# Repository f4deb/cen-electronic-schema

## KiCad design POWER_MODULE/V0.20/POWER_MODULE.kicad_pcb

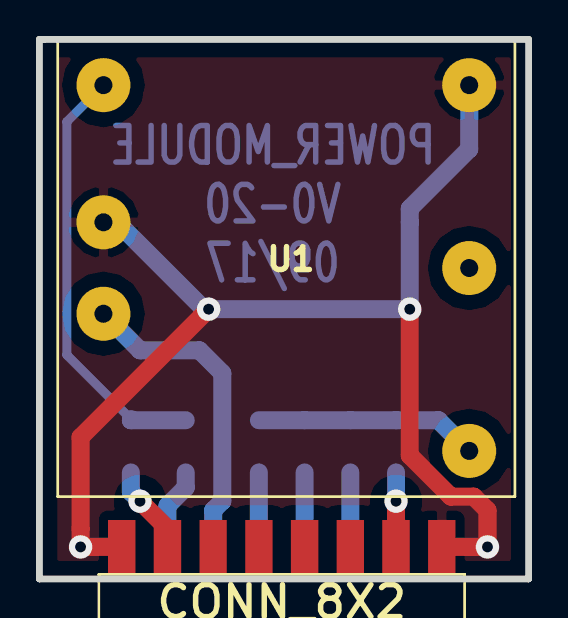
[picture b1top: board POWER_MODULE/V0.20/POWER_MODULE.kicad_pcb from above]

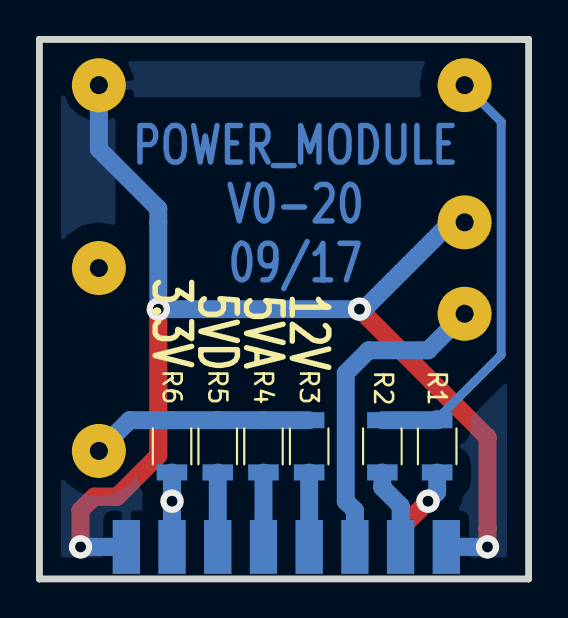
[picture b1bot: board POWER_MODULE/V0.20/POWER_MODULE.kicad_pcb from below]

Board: 2 copper layers, 27.2 x 30.0 mm, 8 parts (6 on the bottom side), 10 nets.

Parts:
P1: CONN_8X2; HE10-16-F-2
R1, R2, R3, R4, R5, R6: 0; R_1206
U1: TRACO-THN-15-1211

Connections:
+3V3: P1.13, P1.14, R6.1
+5V: P1.11, P1.12, R5.1
+5VA: P1.9, P1.10, R4.1
+12V: P1.7, P1.8, R3.1
+BATT: P1.5, P1.6, U1.1
/RA: P1.3, R1.1
/RD: P1.4, R2.1
GND: P1.1, P1.2, P1.15, P1.16, U1.2, U1.5
unnamed: R1.2, R2.2, U1.6
unnamed: R3.2, R4.2, R5.2, R6.2, U1.3

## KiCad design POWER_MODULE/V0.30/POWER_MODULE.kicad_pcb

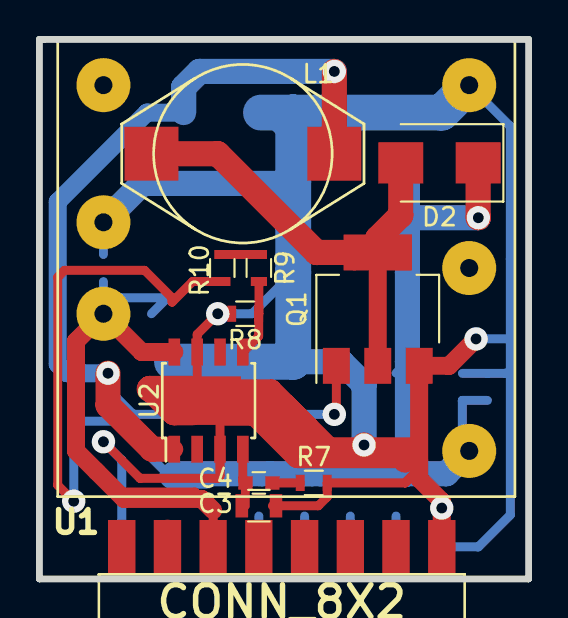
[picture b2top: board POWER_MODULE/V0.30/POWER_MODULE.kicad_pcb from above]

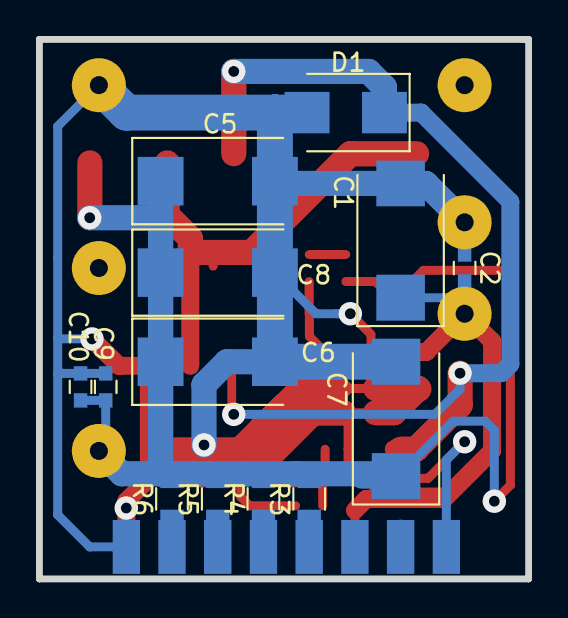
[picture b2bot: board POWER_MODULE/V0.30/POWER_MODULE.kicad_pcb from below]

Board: 2 copper layers, 27.2 x 30.0 mm, 25 parts (13 on the bottom side), 13 nets.

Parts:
C1, C6, C7, C8: 22µ/35V; CP_Tantalum_Case-D_EIA-7343-31_Reflow
C2: 47n; C_0603
C3: 220p; R_0805
C4: 22n; C_0603
C5: 100µ/16V; CP_Tantalum_Case-D_EIA-7343-31_Reflow
C9, C10: 100n; C_0603
D1, D2: MBRS130LT3G; D_SMB
L1: INDUCTOR; self_cms_we-pd3
P1: CONN_8X2; HE10-16-F-2
Q1: IRLL3303; SOT-223
R3, R4, R5, R6: 0; R_0805
R7: 4.7k; R_0603
R8, R9, R10: R; R_0603
U1: TRACO-THN-15-1211
U2: L5973D; Diodes_PSOP-8

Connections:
+3V3: P1.13, P1.14, R6.1
+5V: P1.11, P1.12, R5.1
+5VA: P1.9, P1.10, R4.1
+12V: P1.7, P1.8, R3.1
+BATT: C1.1, C2.1, P1.5, P1.6, U1.1, U2.8
GND: C1.2, C2.2, C3.2, C5.2, C6.2, C7.2, C8.2, C9.2, C10.2, D1.2, P1.1, P1.2, P1.15, P1.16, Q1.3, R7.2, R8.2, U1.2, U1.5, U2.3, U2.7, U2.9
unnamed: C3.1, C4.1, U2.4
unnamed: C4.2, R7.1
unnamed: C5.1, C6.1, C7.1, C8.1, C9.1, C10.1, D2.1, R3.2, R4.2, R5.2, R6.2, R10.1, U1.3
unnamed: D1.1, L1.1, Q1.1, U2.1
unnamed: D2.2, L1.2, Q1.2, Q1.4
unnamed: R8.1, R9.2, U2.5
unnamed: R9.1, R10.2

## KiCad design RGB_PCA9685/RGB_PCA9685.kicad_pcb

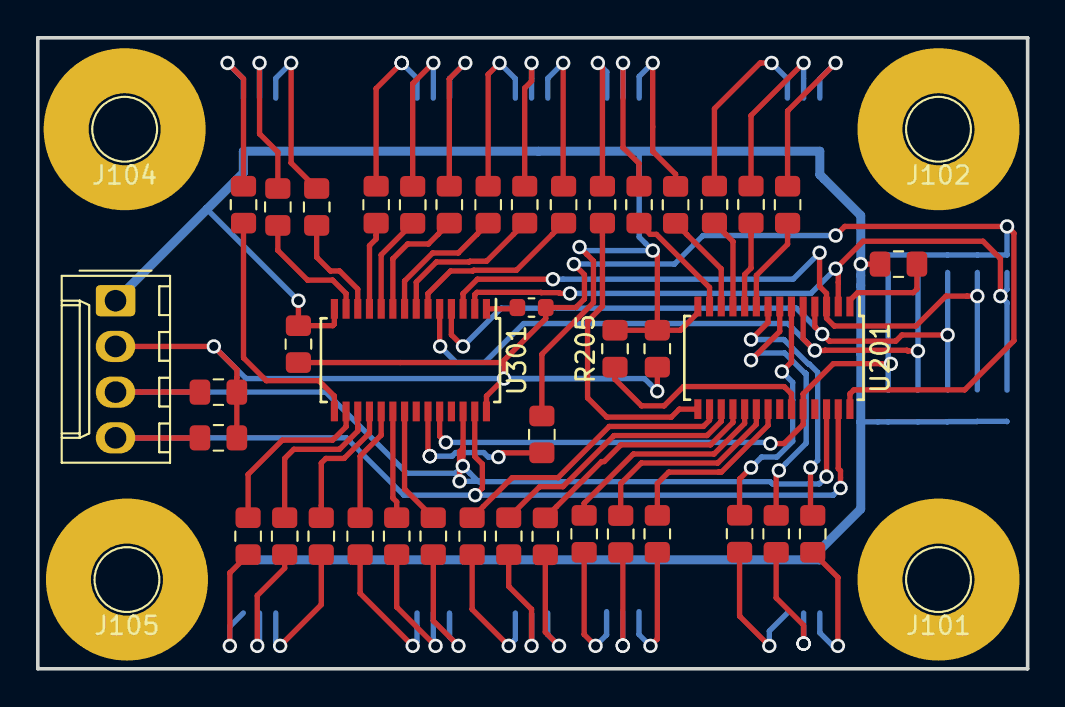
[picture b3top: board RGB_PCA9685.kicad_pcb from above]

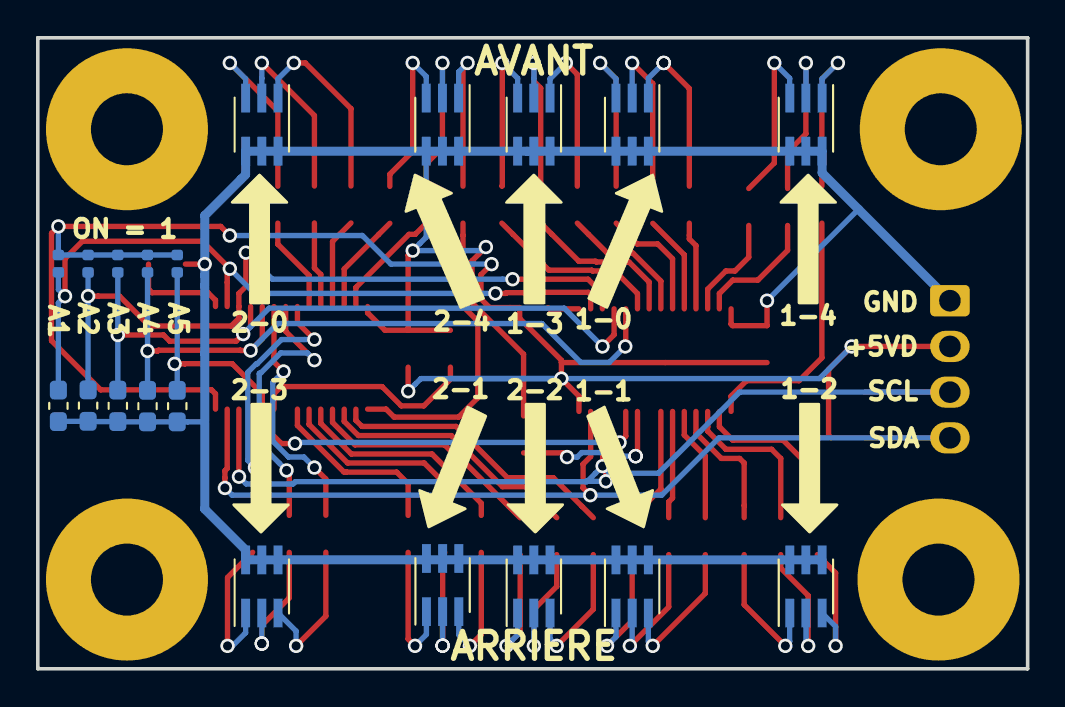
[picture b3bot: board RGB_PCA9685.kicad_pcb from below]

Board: 2 copper layers, 55.0 x 35.1 mm, 65 parts (20 on the bottom side), 73 nets.

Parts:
C201, C301: 100n; C_0805_2012Metric_Pad1.15x1.40mm_HandSolder
D201, D202, D203, D204, D205, D301, D302, D303, D304, D305: ASMT-YTB7-0AA02; LED_Avago_PLCC6_3x2.8mm
J101, J102, J104, J105: Conn_01x01_Female; Pin_D1.3mm_L11.0mm_LooseFit
J103: Conn_01x04; Molex_KK-254_AE-6410-04A_1x04_P2.54mm_Vertical
R101, R103, R105, R107, R109: 0; R_0402_1005Metric
R102, R104, R106, R108, R110: 47k; R_0603_1608Metric_Pad1.05x0.95mm_HandSolder
R205, R207, R209, R305: 10k; R_0805_2012Metric_Pad1.15x1.40mm_HandSolder
R210: 47k; R_0805_2012Metric_Pad1.15x1.40mm_HandSolder
R211, R212, R213, R214, R215, R216, R217, R218, R219, R220, R221, R222, R223, R224, R225, R311, R312, R313, R314, R315, R316, R317, R318, R319, R320, R321, R322, R323, R324, R325: R; R_0805_2012Metric_Pad1.15x1.40mm_HandSolder
R301: 0; R_0603_1608Metric
U201, U301: PCA9685PW; TSSOP-28_4.4x9.7mm_P0.65mm

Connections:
+5VD: C201.1, C301.1, J103.2, R101.1, R103.1, R105.1, R107.1, R109.1, R207.1, R209.1, R301.2, U201.28, U301.28
/RGB_PCA9685-1/A1: R101.2, R102.1, U201.2, U301.2
/RGB_PCA9685-1/A2: R103.2, R104.1, U201.3, U301.3
/RGB_PCA9685-1/A3: R105.2, R106.1, U201.4, U301.4
/RGB_PCA9685-1/A4: R107.2, R108.1, U201.5, U301.5
/RGB_PCA9685-1/A5: R109.2, R110.1, U201.24, U301.24
/RGB_PCA9685-1/B0: R219.2, U201.11
/RGB_PCA9685-1/B1: R211.2, U201.21
/RGB_PCA9685-1/B2: R217.2, U201.18
/RGB_PCA9685-1/B3: R212.2, U201.8
/RGB_PCA9685-1/B4: R218.2, U201.15
/RGB_PCA9685-1/R0: R225.2, U201.9
/RGB_PCA9685-1/R1: R215.2, U201.19
/RGB_PCA9685-1/R2: R223.2, U201.16
/RGB_PCA9685-1/R3: R216.2, U201.6
/RGB_PCA9685-1/R4: R224.2, U201.12
/RGB_PCA9685-1/V0: R222.2, U201.10
/RGB_PCA9685-1/V1: R213.2, U201.20
/RGB_PCA9685-1/V2: R220.2, U201.17
/RGB_PCA9685-1/V3: R214.2, U201.7
/RGB_PCA9685-1/V4: R221.2, U201.13
/RGB_PCA9685-2/B0: R319.2, U301.11
/RGB_PCA9685-2/B1: R311.2, U301.21
/RGB_PCA9685-2/B2: R317.2, U301.18
/RGB_PCA9685-2/B3: R312.2, U301.8
/RGB_PCA9685-2/B4: R318.2, U301.15
/RGB_PCA9685-2/R0: R325.2, U301.9
/RGB_PCA9685-2/R1: R315.2, U301.19
/RGB_PCA9685-2/R2: R323.2, U301.16
/RGB_PCA9685-2/R3: R316.2, U301.6
/RGB_PCA9685-2/R4: R324.2, U301.12
/RGB_PCA9685-2/V0: R322.2, U301.10
/RGB_PCA9685-2/V1: R313.2, U301.20
/RGB_PCA9685-2/V2: R320.2, U301.17
/RGB_PCA9685-2/V3: R314.2, U301.7
/RGB_PCA9685-2/V4: R321.2, U301.13
/SCL: J103.3, R207.2, U201.26, U301.26
/SDA: J103.4, R209.2, U201.27, U301.27
GND: C201.2, C301.2, D201.4, D201.5, D201.6, D202.4, D202.5, D202.6, D203.4, D203.5, D203.6, D204.4, D204.5, D204.6, D205.4, D205.5, D205.6, D301.4, D301.5, D301.6, D302.4, D302.5, D302.6, D303.4, D303.5, D303.6, D304.4, D304.5, D304.6, D305.4, D305.5, D305.6, J103.1, R102.2, R104.2, R106.2, R108.2, R110.2, R205.2, R210.2, R305.2, U201.14, U301.14
unnamed: D201.1, R211.1
unnamed: D201.2, R213.1
unnamed: D201.3, R215.1
unnamed: D202.1, R212.1
unnamed: D202.2, R214.1
unnamed: D202.3, R216.1
unnamed: D203.1, R217.1
unnamed: D203.2, R220.1
unnamed: D203.3, R223.1
unnamed: D204.1, R218.1
unnamed: D204.2, R221.1
unnamed: D204.3, R224.1
unnamed: D205.1, R219.1
unnamed: D205.2, R222.1
unnamed: D205.3, R225.1
unnamed: D301.1, R311.1
unnamed: D301.2, R313.1
unnamed: D301.3, R315.1
unnamed: D302.1, R312.1
unnamed: D302.2, R314.1
unnamed: D302.3, R316.1
unnamed: D303.1, R317.1
unnamed: D303.2, R320.1
unnamed: D303.3, R323.1
unnamed: D304.1, R318.1
unnamed: D304.2, R321.1
unnamed: D304.3, R324.1
unnamed: D305.1, R319.1
unnamed: D305.2, R322.1
unnamed: D305.3, R325.1
unnamed: R205.1, U201.23
unnamed: R210.1, U201.1
unnamed: R301.1, U301.1
unnamed: R305.1, U301.23
